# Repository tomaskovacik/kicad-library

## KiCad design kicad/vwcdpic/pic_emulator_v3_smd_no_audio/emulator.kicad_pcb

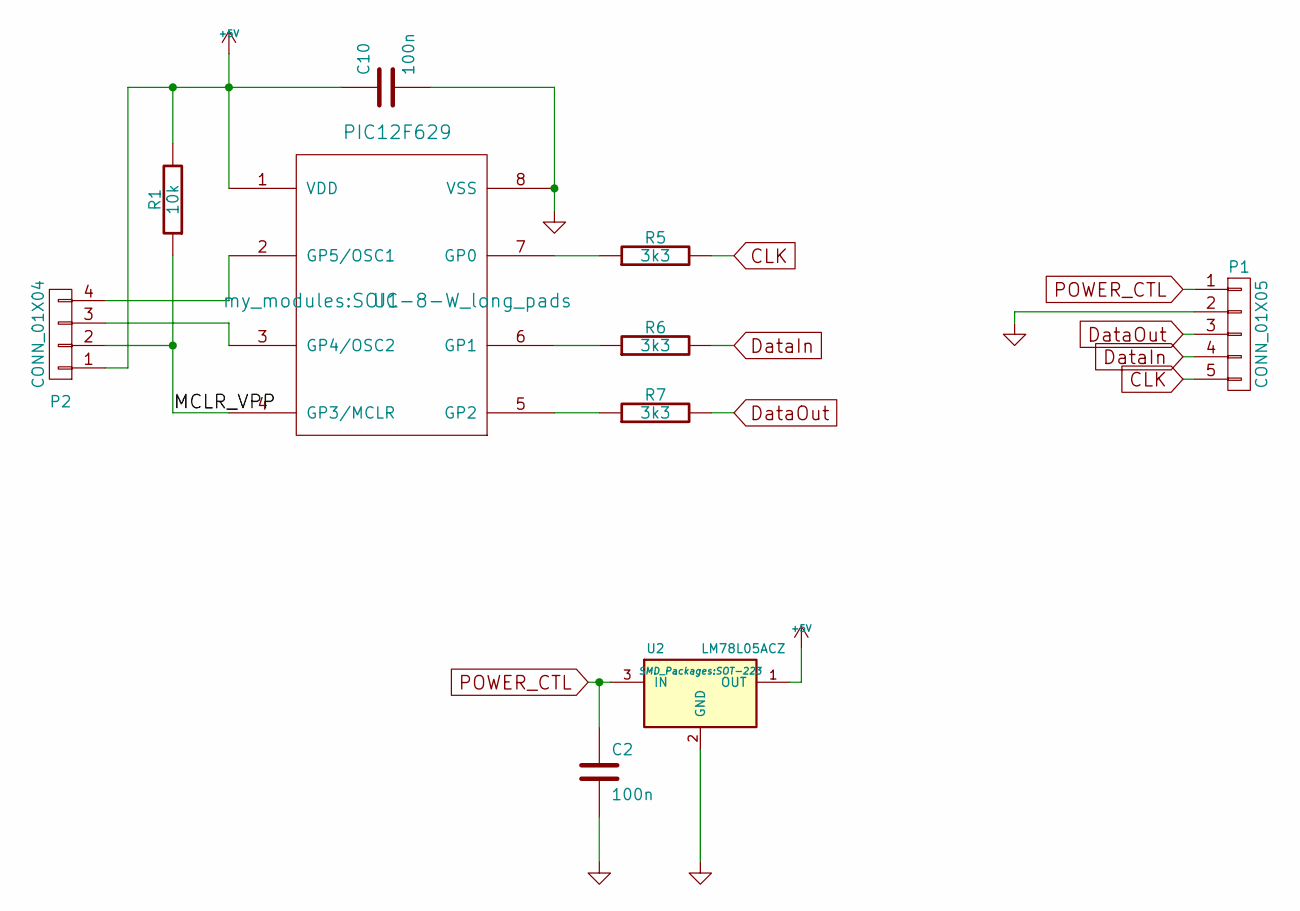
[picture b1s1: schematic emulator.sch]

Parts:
C2, C10: 100n; C_1206_HandSoldering
P1: CONN_01X05; Pin_Header_Straight_1x05
P2: CONN_01X04; Pin_Header_Straight_1x04
R1: 10k; R_1206_HandSoldering
R5, R6, R7: 3k3; R_1206_HandSoldering
U1: PIC12F629; SOIC-8-W_long_pads
U2: LM78L05ACZ; SOT-223

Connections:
+5V: C10.1, P2.1, R1.2, U1.1 (VDD), U2.1 (OUT)
/MCLR_VPP: P2.2, R1.1, U1.4 (GP3/MCLR)
CLK: P1.5, R5.2
DataIn: P1.4, R6.2
DataOut: P1.3, R7.2
GND: C2.2, C10.2, P1.2, U1.8 (VSS), U2.2 (GND), U2.4
unnamed: P2.3, U1.3 (GP4/OSC2)
unnamed: P2.4, U1.2 (GP5/OSC1)
unnamed: R5.1, U1.7 (GP0)
unnamed: R6.1, U1.6 (GP1)
unnamed: R7.1, U1.5 (GP2)
POWER_CTL: C2.1, P1.1, U2.3 (IN)

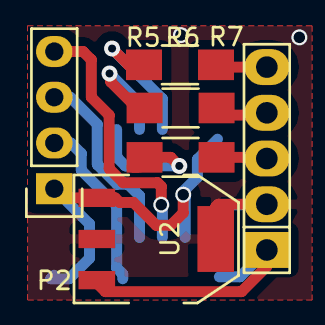
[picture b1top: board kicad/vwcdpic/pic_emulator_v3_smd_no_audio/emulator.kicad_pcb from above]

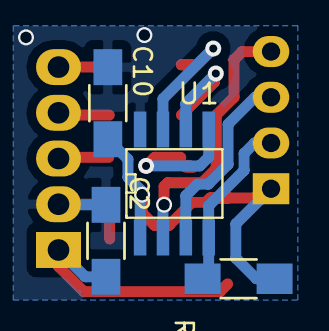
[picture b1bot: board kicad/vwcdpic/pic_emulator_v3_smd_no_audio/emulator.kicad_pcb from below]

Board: 2 copper layers, 10 parts (4 on the bottom side), 12 nets.

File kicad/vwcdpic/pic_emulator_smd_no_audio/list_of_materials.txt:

C10,2    - 100n, 1206
R1       - 10k,  1206
R5,6,7   - 3k3,  1206
U1       - PIC12F629-I/SN, SW: VWCPIC v3, 8SOIC
U2       - AMS-1117-5.0 (5V) SOT-223

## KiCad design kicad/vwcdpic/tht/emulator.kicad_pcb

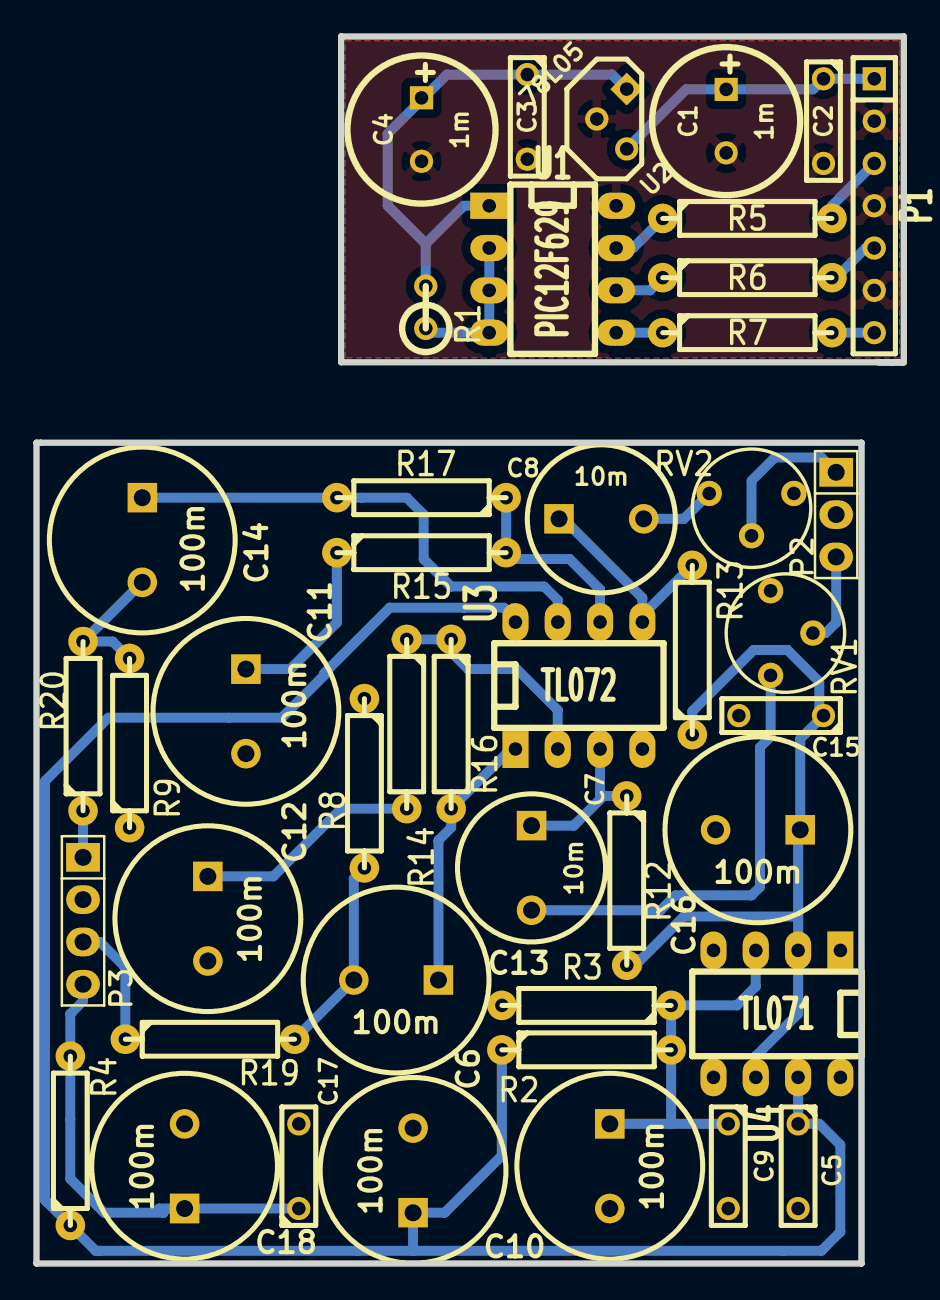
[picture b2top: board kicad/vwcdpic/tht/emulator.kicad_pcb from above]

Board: 2 copper layers, 52.1 x 73.7 mm, 44 parts (0 on the bottom side), 31 nets.

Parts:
C1, C4: 1m; C1.5V8V
C2, C3, C5, C9, C15, C17: 100n; C2
C6, C10, C11, C12, C13, C14, C16, C18: 100m; C2V10
C7, C8: 10m; C2V8
P1: digi; SIL-7
P2: Ain; Pin_Header_Straight_1x03
P3: Aout; Pin_Header_Straight_1x04
R1: 10k; R1
R2, R3, R16, R17: 22k; R4-LARGE_PADS
R4: 10; R4-LARGE_PADS
R5, R6, R7: 3k3; R4-LARGE_PADS
R8, R9, R12, R13: 100k; R4-LARGE_PADS
R14, R15: 2k2; R4-LARGE_PADS
R19, R20: 100; R4-LARGE_PADS
RV1, RV2: 100k; RV2
U1: PIC12F629; DIP-8__300_ELL
U2: 78L05; TO92-123
U3: TL072; DIP-8__300_ELL
U4: TL071; DIP-8__300_ELL

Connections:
+5V: C3.1, C4.1, R1.2, U1.1, U2.3
+6V: C15.1, C16.1, R12.2, R13.1, U4.2, U4.6
+12V: C17.1, C18.1, P3.4, R4.2
AGND: C5.2, C6.2, C9.2, C10.2, C11.2, C12.2, C15.2, C16.2, C17.2, C18.2, P2.2, P3.2, R3.2, R8.1, R9.1, RV1.1, RV2.1, U3.4, U4.4
CLK: P1.3, R5.2
DataIn: P1.5, R6.2
DataOut: P1.7, R7.2
GND: C1.2, C2.2, C3.2, C4.2, P1.2, P1.4, P1.6, U1.8, U2.2
unnamed: C7.1, R12.1, U3.3
unnamed: C7.2, RV1.3
unnamed: C8.1, R13.2, U3.5
unnamed: C8.2, RV2.3
unnamed: C9.1, C10.1, R2.2, R3.1, U4.3
unnamed: C11.1, R15.1
unnamed: C12.1, R14.2
unnamed: C13.1, R16.2, U3.1
unnamed: C13.2, R8.2, R19.2
unnamed: C14.1, R17.2, U3.7
unnamed: C14.2, R9.2, R20.2
unnamed: R1.1, U1.2, U1.3, U1.4
unnamed: R5.1, U1.7
unnamed: R6.1, U1.6
unnamed: R7.1, U1.5
unnamed: R14.1, R16.1, U3.2
unnamed: R15.2, R17.1, U3.6
POWER_CTL: C1.1, C2.1, P1.1, U2.1
filtered_12V: C5.1, C6.1, R2.1, R4.1, U3.8, U4.7
left_in: P2.1, RV2.2
left_out: P3.1, R20.1
right_in: P2.3, RV1.2
right_out: P3.3, R19.1

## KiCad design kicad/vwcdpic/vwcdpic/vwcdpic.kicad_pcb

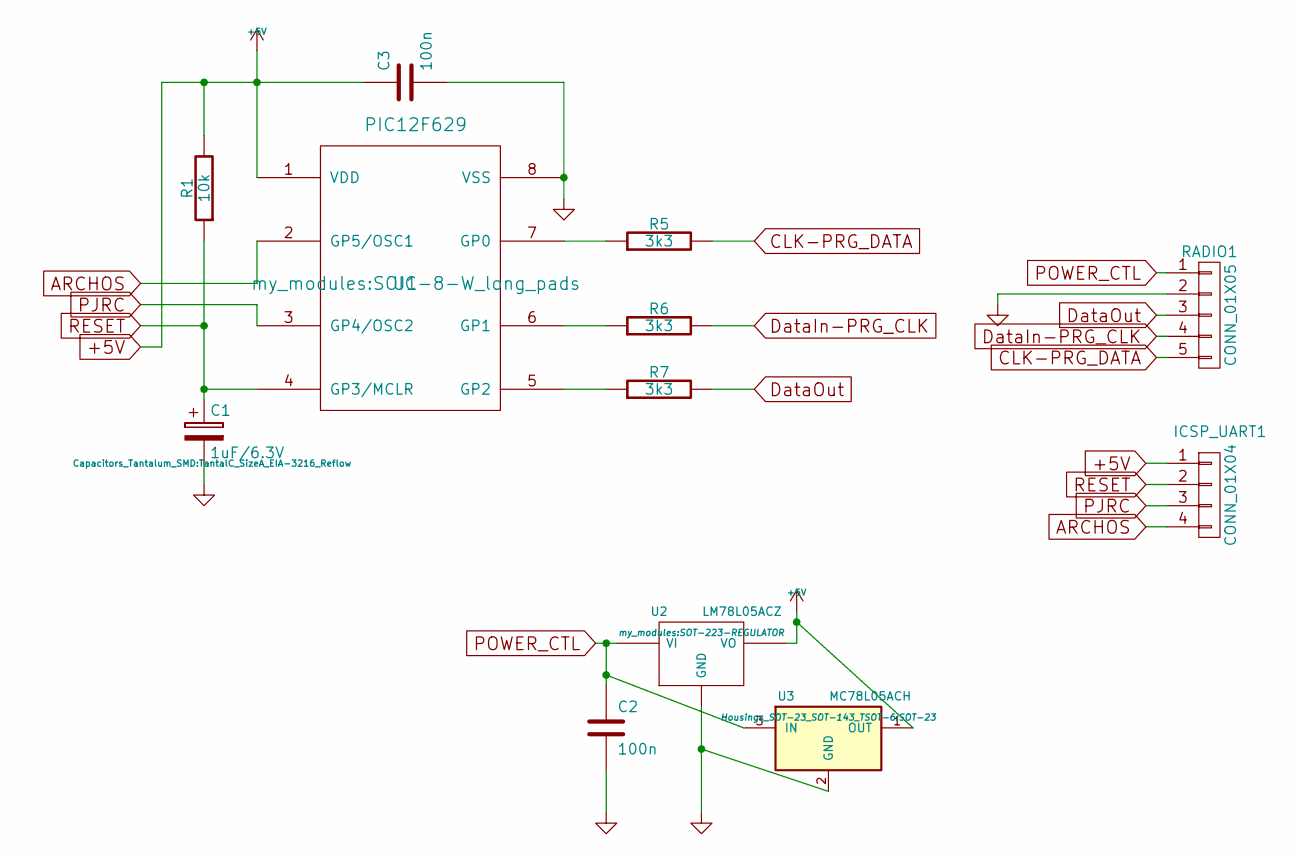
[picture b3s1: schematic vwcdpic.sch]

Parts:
C1: 1uF/6.3V; TantalC_SizeA_EIA-3216_Reflow
C2, C3: 100n; C_0805
ICSP_UART1: CONN_01X04; Pin_Header_Straight_1x04
R1: 10k; R_0805
R5, R6, R7: 3k3; R_0805
RADIO1: CONN_01X05; Pin_Header_Straight_1x05
U1: PIC12F629; SOIC-8-W_long_pads
U2: LM78L05ACZ; SOT-223-REGULATOR
U3: MC78L05ACH; SOT-23

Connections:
+5V: C3.1, ICSP_UART1.1, R1.2, U1.1 (VDD), U2.VO, U3.1 (OUT)
ARCHOS: ICSP_UART1.4, U1.2 (GP5/OSC1)
CLK-PRG_DATA: R5.2, RADIO1.5
DataIn-PRG_CLK: R6.2, RADIO1.4
DataOut: R7.2, RADIO1.3
GND: C1.2, C2.2, C3.2, RADIO1.2, U1.8 (VSS), U2.GND, U3.2 (GND)
unnamed: R5.1, U1.7 (GP0)
unnamed: R6.1, U1.6 (GP1)
unnamed: R7.1, U1.5 (GP2)
PJRC: ICSP_UART1.3, U1.3 (GP4/OSC2)
POWER_CTL: C2.1, RADIO1.1, U2.VI, U3.3 (IN)
RESET: C1.1, ICSP_UART1.2, R1.1, U1.4 (GP3/MCLR)

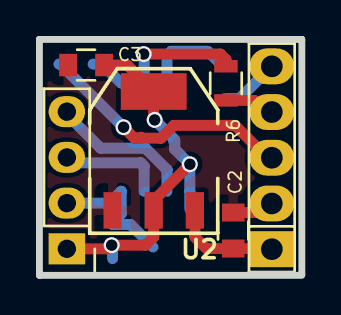
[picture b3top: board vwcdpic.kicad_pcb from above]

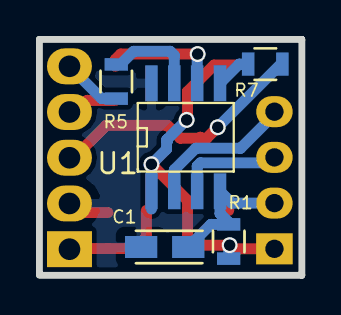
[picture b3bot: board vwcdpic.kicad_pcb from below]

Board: 2 copper layers, 14.6 x 13.1 mm, 11 parts (5 on the bottom side), 12 nets.
